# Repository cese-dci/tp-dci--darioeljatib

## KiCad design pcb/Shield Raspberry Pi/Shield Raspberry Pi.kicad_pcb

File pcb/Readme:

Directorio “pcb” donde se colocará el proyecto Kicad.

Adentro de la carpeta "Shield Raspberry Pi" se encuentra el proyecto completo de KiCad

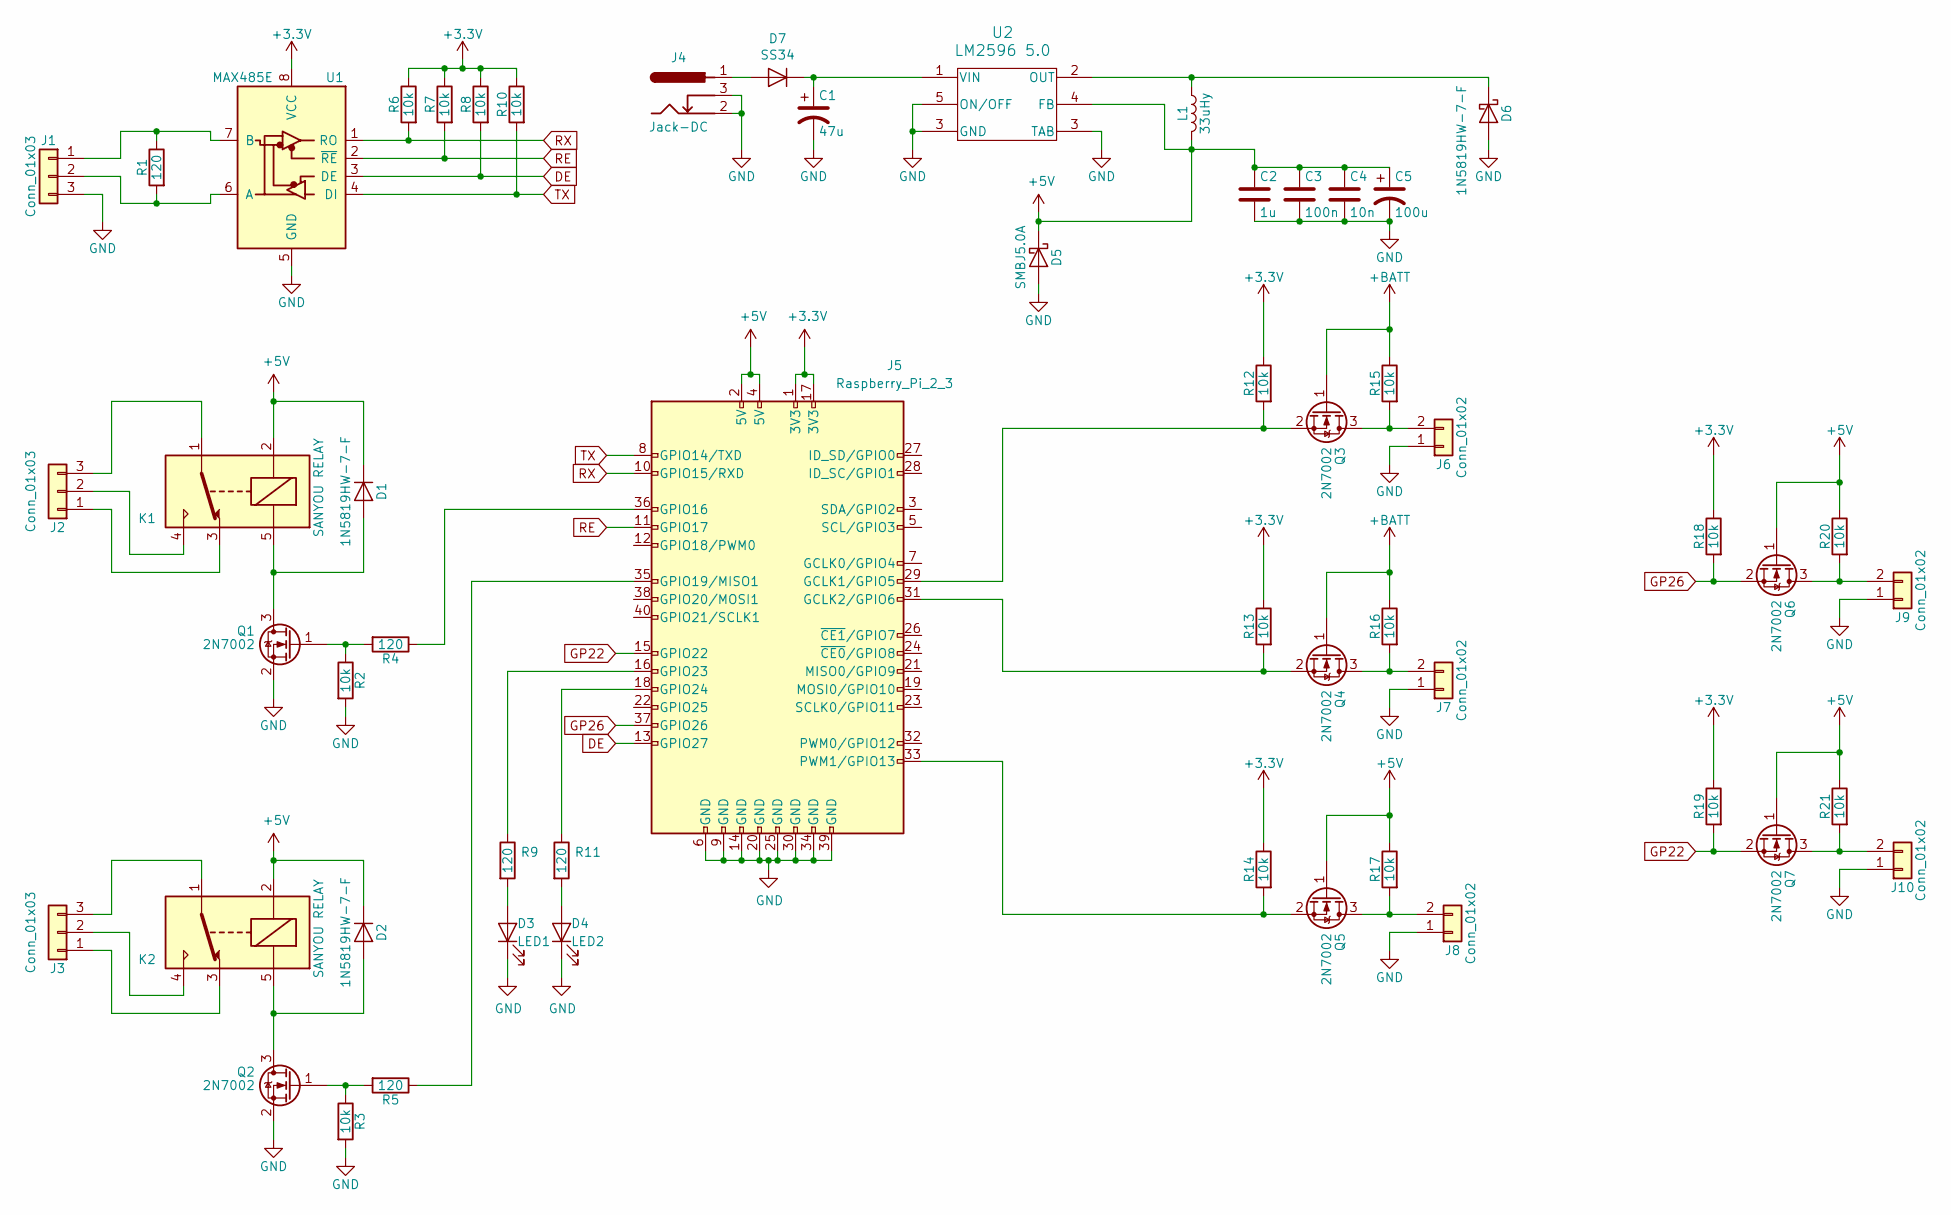
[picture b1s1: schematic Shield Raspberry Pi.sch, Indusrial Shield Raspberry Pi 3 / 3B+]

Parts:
C1: 47u; CP_Radial_D5.0mm_P2.50mm
C2: 1u; C_0805_2012Metric
C3: 100n; C_0805_2012Metric
C4: 10n; C_0805_2012Metric
C5: 100u; CP_Radial_D5.0mm_P2.50mm
D1, D2, D6: 1N5819HW-7-F; D_SOD-123
D3: LED1; LED_0805_2012Metric
D4: LED2; LED_0805_2012Metric
D5: SMBJ5.0A; D_SMB
D7: SS34; D_SMB
J1, J2, J3: Conn_01x03; TerminalBlock_bornier-3_P5.08mm
J4: Jack-DC; BarrelJack_Horizontal
J5: Raspberry_Pi_2_3; PinHeader_2x20_P2.54mm_Vertical
J6, J7, J8, J9, J10: Conn_01x02; TerminalBlock_bornier-2_P5.08mm
K1, K2: SANYOU RELAY; Relay_SPDT_SANYOU_SRD_Series_Form_C
L1: 33uHy; L_Radial_D7.0mm_P3.00mm
Q1, Q2, Q3, Q4, Q5, Q6, Q7: 2N7002; SOT-23
R1, R4, R5, R9, R11: 120; R_0805_2012Metric
R2, R3, R6, R7, R8, R10, R12, R13, R14, R15, R16, R17, R18, R19, R20, R21: 10k; R_0805_2012Metric
U1: MAX485E; SO-8_3.9x4.9mm_P1.27mm
U2: LM2596 5.0; TO-263-5_TabPin3

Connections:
+3V3: J5.1 (3V3), J5.17 (3V3), R6.1, R7.1, R8.1, R10.1, R12.1, R13.1, R14.1, R18.1, R19.1, U1.8 (VCC)
+5V: C2.1, C3.1, C4.1, C5.1, D1.1 (K), D2.1 (K), D5.1 (K), J5.2 (5V), J5.4 (5V), K1.2, K2.2, L1.2, Q5.1 (G), Q6.1 (G), Q7.1 (G), R17.1, R20.1, R21.1, U2.4 (FB)
+BATT: Q3.1 (G), Q4.1 (G), R15.1, R16.1
DE: J5.13 (GPIO27), R8.2, U1.3 (DE)
GND: C1.2, C2.2, C3.2, C4.2, C5.2, D3.1 (K), D4.1 (K), D5.2 (A), D6.2 (A), J1.3, J4.2, J4.3, J5.6 (GND), J5.9 (GND), J5.14 (GND), J5.20 (GND), J5.25 (GND), J5.30 (GND), J5.34 (GND), J5.39 (GND), J6.1, J7.1, J8.1, J9.1, J10.1, Q1.2 (S), Q2.2 (S), R2.2, R3.2, U1.5 (GND), U2.3 (GND), U2.5 (ON/OFF)
GP22: J5.15 (GPIO22), Q7.2 (S), R19.2
GP26: J5.37 (GPIO26), Q6.2 (S), R18.2
unnamed: C1.1, D7.1 (K), U2.1 (VIN)
unnamed: D1.2 (A), K1.5, Q1.3 (D)
unnamed: D2.2 (A), K2.5, Q2.3 (D)
unnamed: D3.2 (A), R9.2
unnamed: D4.2 (A), R11.2
unnamed: D6.1 (K), L1.1, U2.2 (OUT)
unnamed: D7.2 (A), J4.1
unnamed: J1.1, R1.1, U1.7 (B)
unnamed: J1.2, R1.2, U1.6 (A)
unnamed: J2.1, K1.3
unnamed: J2.2, K1.4
unnamed: J2.3, K1.1
unnamed: J3.1, K2.3
unnamed: J3.2, K2.4
unnamed: J3.3, K2.1
unnamed: J5.16 (GPIO23), R9.1
unnamed: J5.18 (GPIO24), R11.1
unnamed: J5.29 (GCLK1/GPIO5), Q3.2 (S), R12.2
unnamed: J5.31 (GCLK2/GPIO6), Q4.2 (S), R13.2
unnamed: J5.33 (PWM1/GPIO13), Q5.2 (S), R14.2
unnamed: J5.35 (GPIO19/MISO1), R5.1
unnamed: J5.36 (GPIO16), R4.1
unnamed: J6.2, Q3.3 (D), R15.2
unnamed: J7.2, Q4.3 (D), R16.2
unnamed: J8.2, Q5.3 (D), R17.2
unnamed: J9.2, Q6.3 (D), R20.2
unnamed: J10.2, Q7.3 (D), R21.2
unnamed: Q1.1 (G), R2.1, R4.2
unnamed: Q2.1 (G), R3.1, R5.2
RE: J5.11 (GPIO17), R7.2, U1.2 (~RE)
RX: J5.10 (GPIO15/RXD), R6.2, U1.1 (RO)
TX: J5.8 (GPIO14/TXD), R10.2, U1.4 (DI)

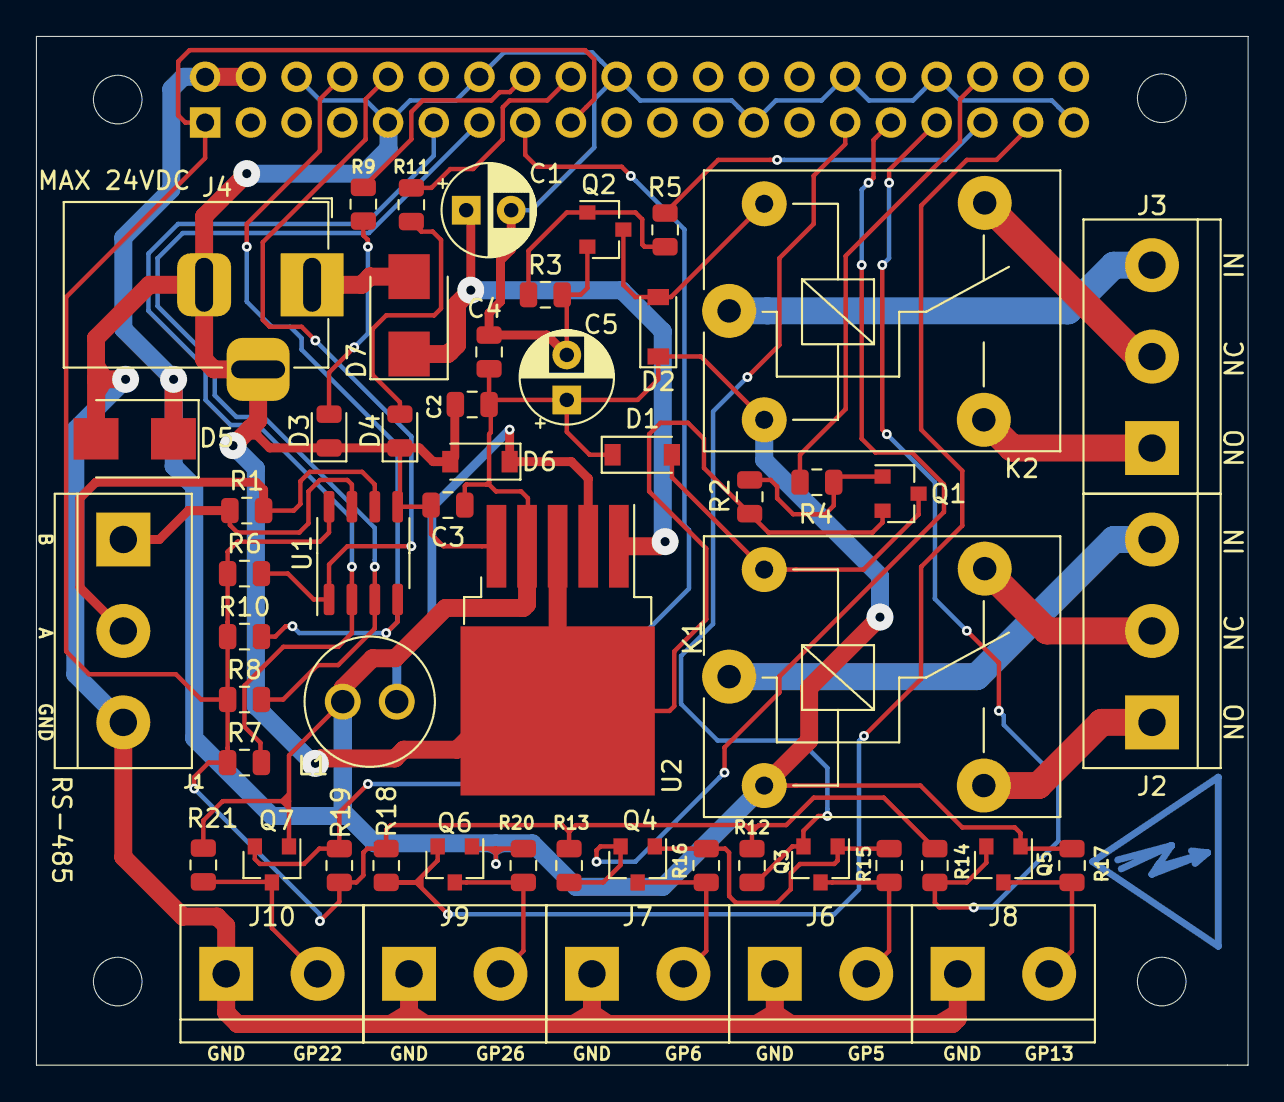
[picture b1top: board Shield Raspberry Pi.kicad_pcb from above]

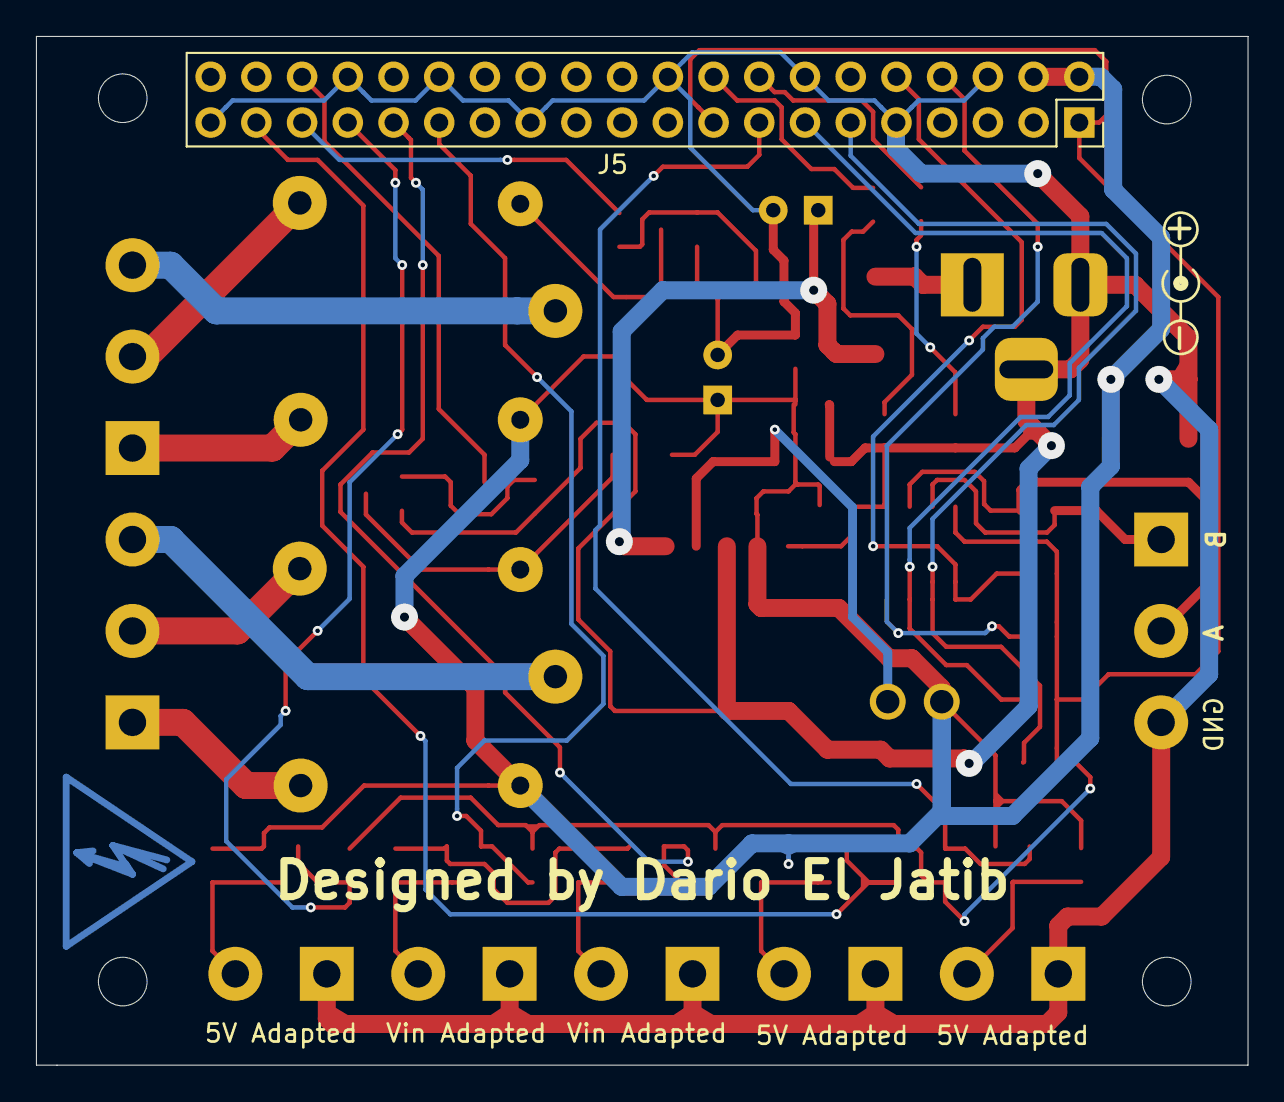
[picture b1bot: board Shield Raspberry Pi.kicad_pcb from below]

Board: 2 copper layers, 67.3 x 57.2 mm, 61 parts (3 on the bottom side), 39 nets.

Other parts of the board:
 : Symbol_HighVoltage_Type2_CopperTop_VerySmall
 #2: Symbol_Barrel_Polarity
 #3,  #4,  #5,  #6: MountingHole_2.7mm

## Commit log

2019-09-13 Add files via upload
    Shield Industrial Raspberry Pi - Diseñado por Dario El Jatib
2019-09-18 Create Explicación
2019-09-19 Update Explicación
2019-09-20 Add files via upload
    Agregado de un 2n7002 y bornera + Ajuste de etiquetas
2019-09-20 Add files via upload
    Agregado de texto
2019-11-14 Falta el ruteo, todo el resto está listo
    Se completó el modelado 3D, se ubicaron todos los componentes, solo falta el ruteo
2019-11-14 Create Logo
2019-11-15 Add files via upload
    Version completamente ruteada, faltan solo algunas leyendas
2019-11-19 Add files via upload
    Proyecto terminado, tiene el ruteo, sin plano de masa, con todas las serigrafías
